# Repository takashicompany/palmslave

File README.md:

# Palmslave (miniDivide v2)

Palmslave(パームスレイブ)は16mm(0.8u)の狭ピッチを採用した38キーで分割型のキーボードです。  
[miniDivide](https://github.com/takashicompany/minidivide)の後継機種となります。  
小さく薄いため持ち運びやすく、特にスマートフォンとの相性は抜群です。  
デスクの占有スペースも小さくて済むので普段遣いにも適しています。  
従来のキーボードよりキーの間隔が近いため、最小限の指の動きで文字を打鍵することが可能です。  

キースイッチはChoc v1とChoc v2に対応しています。
キースイッチソケットを採用しているため、気分や好みにあわせてキースイッチを取り替えることが可能です。
BLE Micro Proを用いることでBluetoothによる無線接続も可能です。  

購入前に以降の作業工程を読みながら頭の中で組み立てるイメージをすることを推奨します。  
部品の位置関係や必要な部品を具体的にすることで、ミスを少なくすることが可能です。  
不明点などありましたら、お気軽にお問い合わせください。

# 紹介記事・動画

購入や組み立ての際に以下のページもご覧頂けますと、より理解が深まるかと思います。

[自作キーボード作ってみた Palmslave編 | Palmslave : Custom Mechanical Keyboard Build](https://www.youtube.com/watch?v=KTx7i8l9HfU&ab_channel=DaihukuKeyboard)

- [GreenKeys : takashicompany新作「Palmslave」レビュー｜スモールデバイスに似合う左右分割無線対応キーボード](https://green-keys.info/takashicompany-palmslave-review/)
- [kazy : 狭ピッチ40%分割キーボード「Palmslave」ビルドログ](https://note.com/kazy_developer/n/n3b10e4a06097)
- [Kinotsuyo : 持ち運びたくなる狭ピッチキーボード、Palmslaveの魅力](https://kino-tsuyo.com/palmslave/)

# 部品

## キットに含まれているもの

|部品|個数|備考|
|:--|:--|:--|
|基板|2||
|[ダイオード(表面実装型)](https://shop.yushakobo.jp/collections/all-keyboard-parts/products/a0800di-02-100)|38||
|[スイッチソケット Choc用](https://shop.yushakobo.jp/products/a01ps?variant=37665172553889)|38|[取り付けの向きがありますので、ご注意ください。](https://www.eisbahn.jp/yoichiro/2021/01/kailh_choc_v1_socket.html#gsc.tab=0)|
|[タクトスイッチ](https://akizukidenshi.com/catalog/g/gP-08081/)|2||
|[TRRSソケット](https://shop.yushakobo.jp/products/a0800tr-01-1?_pos=1&_sid=6aacd8367&_ss=r)|2||
|ゴム足シール|8||
|[チップ積層セラミックコンデンサー](https://akizukidenshi.com/catalog/g/gP-02151/)|2|BLE Micro Proでの無線化の際に使用。|
|[電源スイッチ(MK12C02)](https://ja.aliexpress.com/item/32798526843.html)|2|BLE Micro Proでの無線化の際に使用。|
|[HU1632](https://www.monotaro.com/p/8835/2765/)|2|BLE Micro Proでの無線化の際に使用。|
|短いネジ(M2 6mm)|12||
|長いネジ(M2 10mm)|12||
|ナット(M2)|12||
|長いスペーサー(M2 8mm)|6||

## ご自身で用意頂くもの

### 部品

|部品|個数|備考|
|:--|:--|:--|
|[キースイッチ](https://shop.yushakobo.jp/collections/all-switches/products/pg1350)|38|Choc v1、v2に対応しています。Lofreeのキースイッチにも対応しています。|
|0.8uキーキャップ(16mm)|38|[こちら](https://zenn.dev/takashicompany/articles/9ed4ea07e072fd)にまとめております。|
|[Pro Micro](https://shop.yushakobo.jp/products/3905)|2|動作確認済みのものは[こちら](https://shop.yushakobo.jp/products/3905)です。高さがあるPro Micro(USB-C採用をしたものなど)はPro Microカバーと干渉してしまうことがあります。背の低いPro Microを選択するかスペーサーを長いものに取り替えるなどで対応できます。またBLE Micro Proと[BMP Boost](https://shop.yushakobo.jp/products/10737)は互換性を維持しており、当キーボードでも[BMP Boostで動作することが確認](https://x.com/takashicompany/status/1981351390409904529?s=20)されております。|
|[コンスルー](https://shop.yushakobo.jp/products/31)|4|12ピンのものを購入しておけばPro Micro、BLE Micro Proの両方に用いることができます。|
|[TRRSケーブル](https://shop.yushakobo.jp/products/8023)|1|有線接続の際に左右のキーボードを接続します。**ケーブルが太いものはケースと干渉してしまうことがありますので、左右接続を有線で行う場合は[細身のケーブル](https://shop.yushakobo.jp/products/8023)をご利用ください。**|

### ケース

ケースはアクリルケースと3Dプリントケースの2種類となります。

#### アクリルケース

データは[こちら](https://github.com/takashicompany/palmslave/tree/master/case/acrylic-plate)です。  
[遊舎工房の「キーボードアクリルプレート」](https://shop.yushakobo.jp/products/keyboard_acrylic_plate?variant=50646933897447)にて発注可能です。  

|部品|個数|備考|
|:--|:--|:--|
|スイッチプレート|2|2mm厚アクリルプレート。|
|側面プレート|2|2mm厚アクリルプレート。|
|ボトムプレート|2|2mm厚アクリルプレート。|
|MCUカバー(Pro Microプレート)|2|2mm厚アクリルプレート。|

#### 3Dプリントケース

データは[こちら](https://github.com/takashicompany/palmslave/tree/master/case/3d-print)です。

|部品|個数|備考|
|:--|:--|:--|
|スイッチプレート(トッププレート)|2||
|ボトムプレート|2||
|MCUカバー(Pro Microプレート)|2||

### キーキャップ

[こちら](https://zenn.dev/takashicompany/articles/9ed4ea07e072fd)にてまとめております。  
キースイッチは中心を16mm間隔で配置しておりますので、15.5mmサイズのキーキャップであれば問題なく利用できるかと思います。  

# 組み立て方

## 1. 基板の左右と表裏を確認する

基板はリバーシブル構造となっています。作業ミスを減らすためにマスキングテープなどで表面に左右が分かるように記入することを推奨します。

## 2. ダイオードの取り付け

ダイオードを取り付けます。ダイオードはキースイッチの入力を伝達するのに必要な機構です。基板の裏面に取り付けます。  

ダイオードには向きがあります。基板に `[□ ▷|□]` と印刷された箇所に取り付けます。この時 `▷|` の縦線とダイオードの縦線が同じ側になるように配置します。  

ダイオードを取り付ける前に、ダイオード配置箇所のハンダ付け面の片方にハンダを溶かして乗せておきます。(予備ハンダ)

ピンセットでダイオードを掴みながら予備ハンダを溶かしてダイオードの片側を基板とハンダ付けします。  

もう一方もハンダ付けします。  

基板の片側で19箇所、左右で38箇所にダイオードをハンダ付けしたら完了です。

## 3. キースイッチソケットの取り付け

キースイッチソケットを基板に取り付けます。キースイッチソケットはキースイッチを固定するために使用する部品です。基板の裏面に取り付けます。  

ダイオードと同様にハンダ付け箇所の片側に予備ハンダをします。  

ピンセットでキースイッチソケットを掴みながら予備ハンダを溶かしてキースイッチソケットをハンダ付けします。

反対側もハンダ付けします。  

こちらダイオードと同様に片側で19箇所、左右で38箇所に取り付けます。  

## 4. リセットスイッチの取り付け

リセットスイッチとして、タクトスイッチを基板に取り付けます。リセットスイッチはファームウェアを書き込む際に利用します。  

リセットスイッチの取付箇所は基板の裏側になります。  

ダイオードやキースイッチソケットと同様に、タクトスイッチのハンダ付け箇所の1つに予備ハンダをします。  

ピンセットでタクトスイッチを掴みながら予備ハンダを溶かしてハンダ付けします。  

タクトスイッチ足4つ全てをハンダ付けします。左右の基板どちらにも取り付けてください。  

## 5. Pro Microの取り付け

MCU（Micro Controller Unit）として、Pro Microを取り付けます。MCUは主にキーボードの入力をPCなどの外部デバイスに伝達します。Palmslaveは BLE Micro Proを用いた無線化に対応していますが、動作が正しくない場合のトラブルシューティングの観点から最初はPro Microによる有線接続で組み立てることを推奨します。  

Pro Microを基板に取り付ける際は[コンスルー](https://shop.yushakobo.jp/products/31)を使用することを強く推奨します。コンスルーを用いることでMCUが故障した歳の交換が容易になる・Pro Microを用いて組み立てた後にBLE Micro Proへの移行が容易になります。  

コンスルーを基板に表側に挿します(ハンダ付けなどはしないでください）。Pro Microを指す場合は奥側(写真では右下)のBATとGNDのピン穴は空けておきます。  

コンスルーにPro Microを載せます。コンスルーを載せる際には基板のピンの印字とPro Microのピンの印字が合致することを確認してください。**左手側と右手側でPro Microの表裏が異なります。** [こちらのPro Micro](https://shop.yushakobo.jp/products/pro-micro)では **左手側にはPro Microの部品が基板側になるように配置します。** **右手側はPro Microの部品が表側になるように配置します。** 以降は左手側の取り付け例となります。  

コンスルーとPro Microをハンダ付けします。Pro Microによってはハンダ付けをせずに導通できるものもあります。BLE Micro Proの場合もハンダ付けは不要です。  

右手側も同様の手順で取り付けます。先述した通り右手側はPro Microの表裏が逆になります。  

## 6. TRRSソケットの取り付け

左右のキーボードをTRRSケーブルで接続する際のTRRSソケットを取り付けます。  

TRRSソケットを基板の表側に載せます。  

基板を裏返してTRRSソケットの足が基板裏面から出ていることを確認します。4つの足が出ている状態が正しいです。  

基板とTRRSソケットの足をハンダ付けします。  

## 7. ファームウェアの書き込み

Pro Microにファームウェアを書き込みます。ファームウェアは[Remapから書き込む](https://remap-keys.app/catalog/9hMciuSoDHS5Mp3YbabX/firmware)ことができます。

Remapでのファームウェア書き込みは[こちら](https://docs.dailycraft.jp/buildguides/firmware/remap.html)を参照すると手順が分かりやすいかと思います。

Remapの使い方は[こちら](https://salicylic-acid3.hatenablog.com/entry/remap-manual)を参照するのが分かりやすいかと思います。

Remapでダイオードとスイッチソケット、Pro Microが正しく動作するかを確認できます。USBでPCに接続しRemapを開いた後に、右下の3点リーダからTest Matrix modeを選択してください。  

金属製のピンセットなどで赤丸の箇所を通電させることで擬似的にキースイッチの入力を再現できます。  

全てのキースイッチが点灯するかを確認します。なお、ファームウェアは左手側をUSBとして接続することを前提としているので、片手側のみを接続した場合は左手側が点灯します。  

もし点灯しないキーがあった場合はダイオードやスイッチソケットのハンダ付けを再度行うと改善することがあるかと思います。

## 8. 無線化用の部品の取り付け

この項目は**Pro Microでの有線接続で左右のキーボードの全てのキーの入力が確認できた後に実施することを推奨**します。
無線化自体は組み立て終わった後でも実施可能ですので、後回しにしてもOKです。

チップ積層セラミックコンデンサーを取り出します。  

取り付け箇所は基板裏側のリセットスイッチ付近です。  

ダイオードなどと同様に予備ハンダを行います。  

ピンセットでコンデンサーを掴みながら予備ハンダを溶かしつつ片側をハンダ付けします。  

コンデンサーのもう片側もハンダ付けを行います。  

電源スイッチを取り出します。取り付け箇所は基板の裏面のタクトスイッチ付近です。

電源スイッチの足と基板のハンダ付け箇所が合うように載せます。  

電源スイッチの足と基板をハンダ付けします。  

コイン電池ホルダーを取り付けます。取り付け箇所は基板の表側のPro MicroとTRRSソケットの間です。  

コイン電池ホルダーの足が基板に通るように穴を確認しながら挿します。  

基板の裏面からコイン電池ホルダーの足が出ていることを確認します。基板を裏返した時にコイン電池ホルダーが抜け落ちしまう場合はマスキングテープなどで固定すると作業がスムーズに進められます。赤丸の位置からコイン電池ホルダーの足が出ていることを確認できたら足と基板をハンダ付けします。  

コイン電池ホルダーにCR1632を入れます。Pro Microと同様にBLE Micro Proを取付けます。

Pro Microは片側12ピンですが、BLE Micro Proは13ピンとなります。12ピンのコンスルーのみのお持ちの方はBATの穴にコンスルーのピンが来るように挿してください(取り付け例は[こちら](https://x.com/takashicompany/status/1906256170035408966))。なお、BLE Micro Proとコンスルー、基板はハンダ付けなしで取り付けが可能です。

BLE Micro Proの設定手順は[こちら](https://sekigon-gonnoc.github.io/BLE-Micro-Pro/#/getting_started?id=ble-micro-pro-web-configurator%e3%82%92%e4%bd%bf%e3%81%a3%e3%81%a6%e3%83%95%e3%82%a1%e3%83%bc%e3%83%a0%e3%82%a6%e3%82%a7%e3%82%a2%e3%82%92%e6%9b%b8%e3%81%8d%e8%be%bc%e3%82%80)を参考に進めてください。

## 9. ケースとキースイッチの取り付け

以降は左手側での組み立て説明です。右手側も手順は同様です。
アクリルケースと3Dプリントケースの2種類での組み方の説明となります。
大まかな部分の手順は同様ですので、どちらの手順も目を通しておくと理解度が高まります。

### アクリルケース

以下5つの部品を用いて組み立てます。保護シートが貼られている場合は剥がしてください。  

①スイッチプレートをキースイッチを用いて取り付けます。基板の表側に配置します。  

スイッチプレートと基板をキースイッチを用いて固定します。  

スイッチプレートを基板の表側に載せ、キースイッチをスイッチプレートに挿します。この時キースイッチの足がスイッチソケットに入るように挿します。スイッチは4-5個程度用いて仮止めとします。  

②ボトムプレートと⑤スペーサープレートを用意します。    

スペーサーと短いネジを2本用意します。  

裏面からネジを挿してスペーサーを用いてスペーサープレートと固定します。  

表面からは以下の写真と同様になっていればOKです。  

ボトムプレートに③積層プレートAを載せ、さらにその上に④積層プレートBを重ねます。  

スペーサーに加え、長いネジとナットを用います。  

Pro Micro横のネジ穴は長いネジを裏面から通して表面からスペーサーで固定します。スペーサーは積層プレートAに載せる形となります。  

他のネジ穴はスイッチプレートから積層プレートA & B → ボトムプレートと通します。

裏返して、ボトムプレートから出たネジをナットで止めます。  

### 3Dプリントケース

スイッチプレートを用意します。  

スイッチプレートと基板をキースイッチで固定します。  

キースイッチを4-5個程度スイッチプレートに挿します。  

基板の上にスイッチプレートを載せ、先ほど挿したキースイッチの足が基板に取り付けたキースイッチソケットに刺さるようにはめ込みます。  

全てのキースイッチを取り付けます。  

ボトムプレートを取り出します。  

先程のスイッチプレート(と基板)にボトムプレートをはめ込みます。  

長いネジとナットを取り出します。  

ネジをスイッチプレートの表面からネジ穴に挿します。  

裏返してボトムプレートから先ほど挿したネジをナットで留めます。  

短いネジとスペーサーを取り出します。  

ボトムプレートの赤丸の箇所に短いネジを挿します。  

表面から先程挿したネジをスペーサーで固定します。  

### Pro Microカバーの取り付け

以降はアクリルケース・3Dプリントケースのどちらも手順は共通です。  
Pro Microカバーを取り出します。  

スペーサーの上にPro Microカバーを載せ、短いネジで固定します。  

## 10. ゴム足シールの取付け

ケースの底面に滑り止めとしてゴム足シールを貼り付けます。  

打鍵スタイルにあわせてお好みの位置に貼り付けてください。  

## 11. キーキャップの取り付け

キースイッチにキーキャップを取付けて完成です。  

### 12. 完成した後の楽しみ方

完成しましたら、ぜひSNSなどに写真を投稿頂ければと思います。
Twitterのハッシュタグは [`#Palmslave #自作キーボード`](https://twitter.com/search?q=%23%E8%87%AA%E4%BD%9C%E3%82%AD%E3%83%BC%E3%83%9C%E3%83%BC%E3%83%89%20%23Palmslave&src=typed_query) を付けていただけると幸いです。
キットを組み立てた感想や、キーボードを使った所感などをお待ちしております！

また、毎週日曜日の１9時より実施されている[#KEEP_PD](https://twitter.com/hashtag/KEEB_PD?f=live)に投稿頂くこともオススメです。  
開催の告知は[@KEEB_PD](https://twitter.com/KEEB_PD)にて行われております。

ご不明な点などございましたら、[@takashicompany](https://twitter.com/takashicompany)にメンションやDM頂ければ回答できるかと思います。

<!--

-->

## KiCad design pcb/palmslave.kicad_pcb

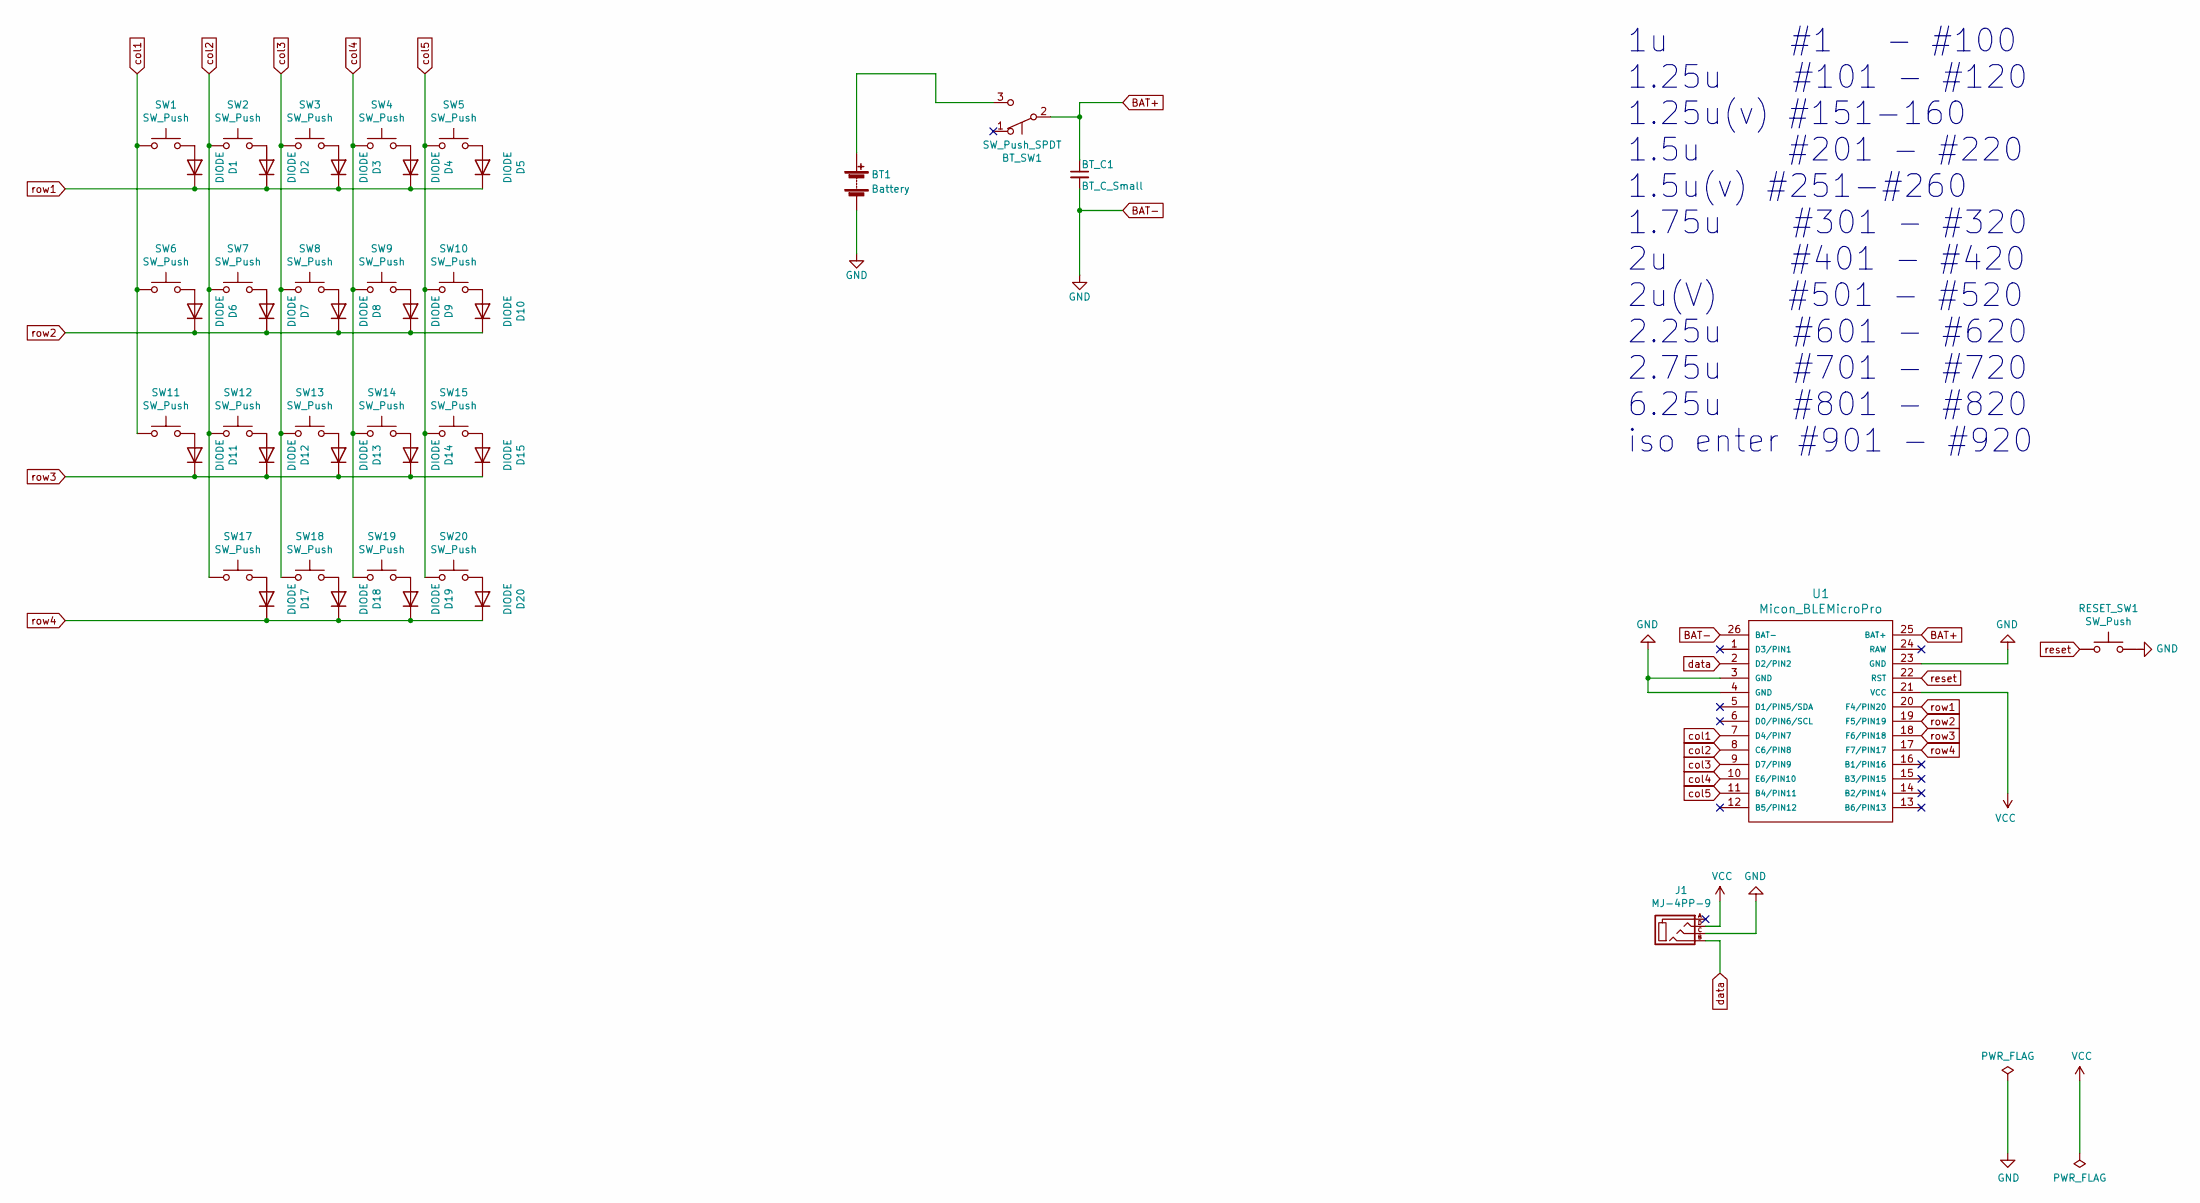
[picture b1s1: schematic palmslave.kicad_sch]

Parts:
BT1: Battery; HU1632_Reversible
BT_C1: BT_C_Small; C_1206_HandSoldering_Reversible
BT_SW1: SW_Push_SPDT; MK12C02_Reversible_SameOn
D1, D2, D3, D4, D5, D6, D7, D8, D9, D10, D11, D12, D13, D14, D15, D17, D18, D19, D20: DIODE; D3_SMD_v2_Reversible
J1: MJ-4PP-9; MJ-4PP-9_v2
RESET_SW1: SW_Push; TVAF17-WFC-R_2pin_Reversible
SW1, SW2, SW3, SW4, SW5, SW6, SW7, SW8, SW9, SW10, SW11, SW12, SW13, SW14, SW15, SW17, SW18, SW19, SW20: SW_Push; ChocV1_V2_Hotswap_16mm_Reversible_2Side
U1: Micon_BLEMicroPro; BLE-Micro-Pro_r_print-inside

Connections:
BAT+: BT_C1.1, BT_SW1.2 (B), U1.25 (BAT+)
BAT-: BT1.2 (-), BT_C1.2, J1.C, RESET_SW1.2, U1.3 (GND), U1.4 (GND), U1.23 (GND), U1.26 (BAT-)
unnamed: BT1.1 (+), BT_SW1.3 (C)
unnamed: D1.2 (A), SW1.2
unnamed: D2.2 (A), SW2.2
unnamed: D3.2 (A), SW3.2
unnamed: D4.2 (A), SW4.2
unnamed: D5.2 (A), SW5.2
unnamed: D6.2 (A), SW6.2
unnamed: D7.2 (A), SW7.2
unnamed: D8.2 (A), SW8.2
unnamed: D9.2 (A), SW9.2
unnamed: D10.2 (A), SW10.2
unnamed: D11.2 (A), SW11.2
unnamed: D12.2 (A), SW12.2
unnamed: D13.2 (A), SW13.2
unnamed: D14.2 (A), SW14.2
unnamed: D15.2 (A), SW15.2
unnamed: D17.2 (A), SW17.2
unnamed: D18.2 (A), SW18.2
unnamed: D19.2 (A), SW19.2
unnamed: D20.2 (A), SW20.2
VCC: J1.D, U1.21 (VCC)
col1: SW1.1, SW6.1, SW11.1, U1.7 (D4/PIN7)
col2: SW2.1, SW7.1, SW12.1, SW17.1, U1.8 (C6/PIN8)
col3: SW3.1, SW8.1, SW13.1, SW18.1, U1.9 (D7/PIN9)
col4: SW4.1, SW9.1, SW14.1, SW19.1, U1.10 (E6/PIN10)
col5: SW5.1, SW10.1, SW15.1, SW20.1, U1.11 (B4/PIN11)
data: J1.B, U1.2 (D2/PIN2)
reset: RESET_SW1.1, U1.22 (RST)
row1: D1.1 (K), D2.1 (K), D3.1 (K), D4.1 (K), D5.1 (K), U1.20 (F4/PIN20)
row2: D6.1 (K), D7.1 (K), D8.1 (K), D9.1 (K), D10.1 (K), U1.19 (F5/PIN19)
row3: D11.1 (K), D12.1 (K), D13.1 (K), D14.1 (K), D15.1 (K), U1.18 (F6/PIN18)
row4: D17.1 (K), D18.1 (K), D19.1 (K), D20.1 (K), U1.17 (F7/PIN17)

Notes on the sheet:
1u #1 - #100 1.25u #101 - #120 1.25u(v) #151-160 1.5u #201 - #220 1.5u(v) #251-#260 1.75u #301 - #320 2u #401 - #420 2u(V) #501 - #520 2.25u #601 - #620 2.75u #701 - #720 6.25u #801 - #820 iso enter #901 - #920

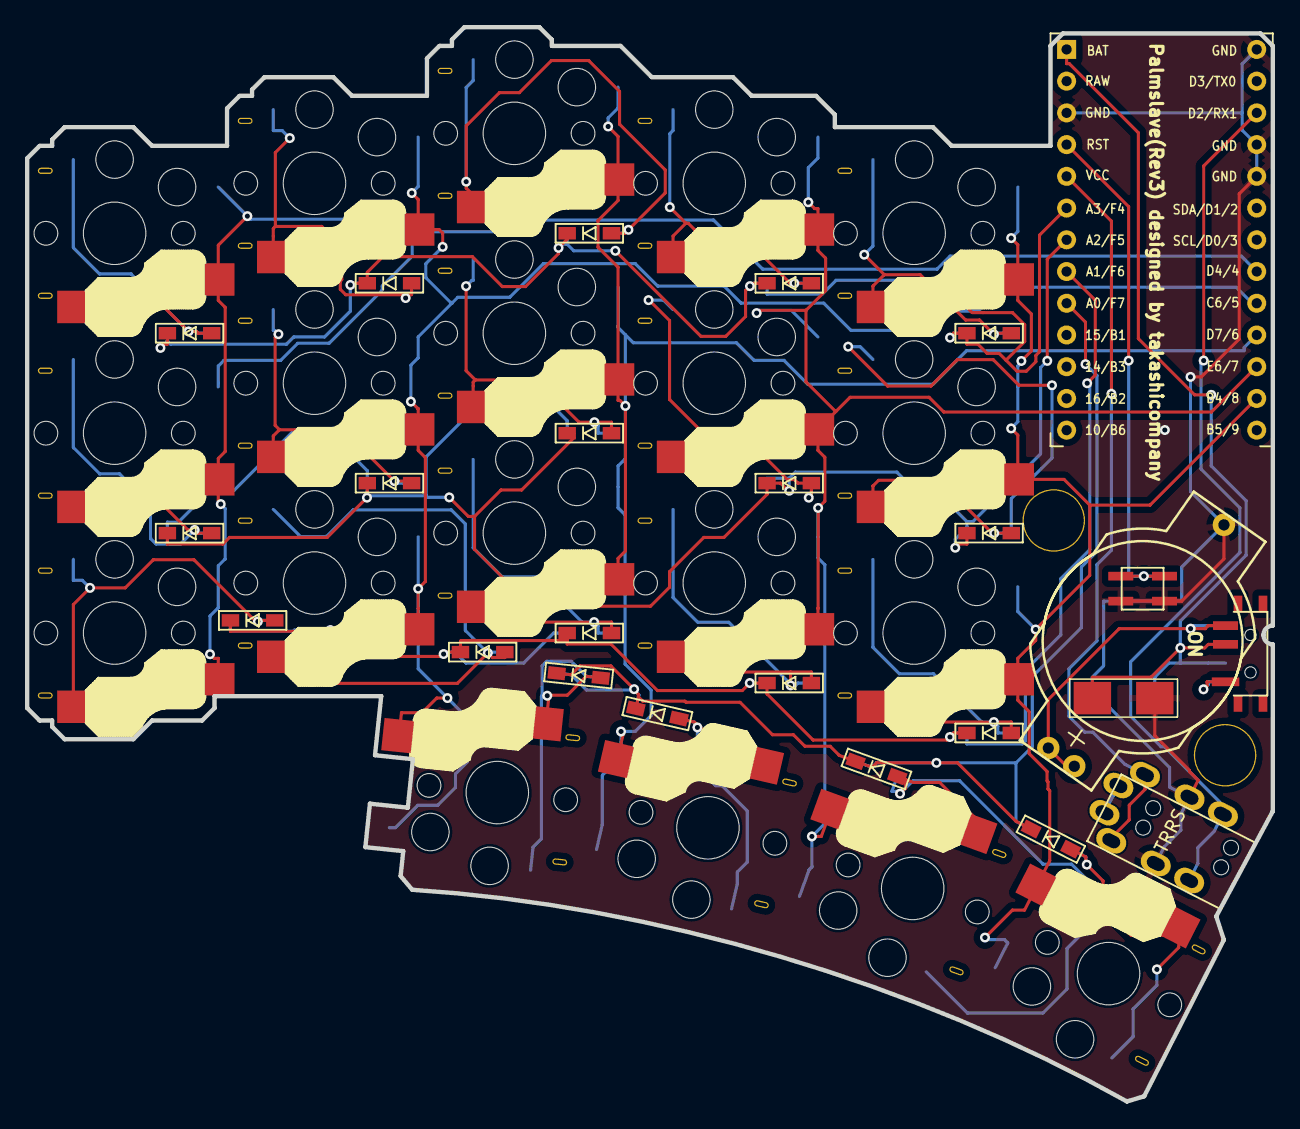
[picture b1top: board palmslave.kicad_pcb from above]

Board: 2 copper layers, 99.7 x 86.0 mm, 46 parts (0 on the bottom side), 34 nets.

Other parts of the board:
Hole02, Hole03: Val**; HOLE

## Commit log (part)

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2025-01-10 画像を追加
2025-01-12 写真を追加
2025-01-12 字を書いた
2025-01-12 画像を直した
2025-01-13 赤丸を追加
2025-03-29 case
2025-04-18 3d-print
2025-04-18 cc-by-sa
2025-04-18 アクリルプレート
2025-04-18 kawamura photo
2025-04-18 Daihuku photo
2025-07-05 kinotsuyo photos
